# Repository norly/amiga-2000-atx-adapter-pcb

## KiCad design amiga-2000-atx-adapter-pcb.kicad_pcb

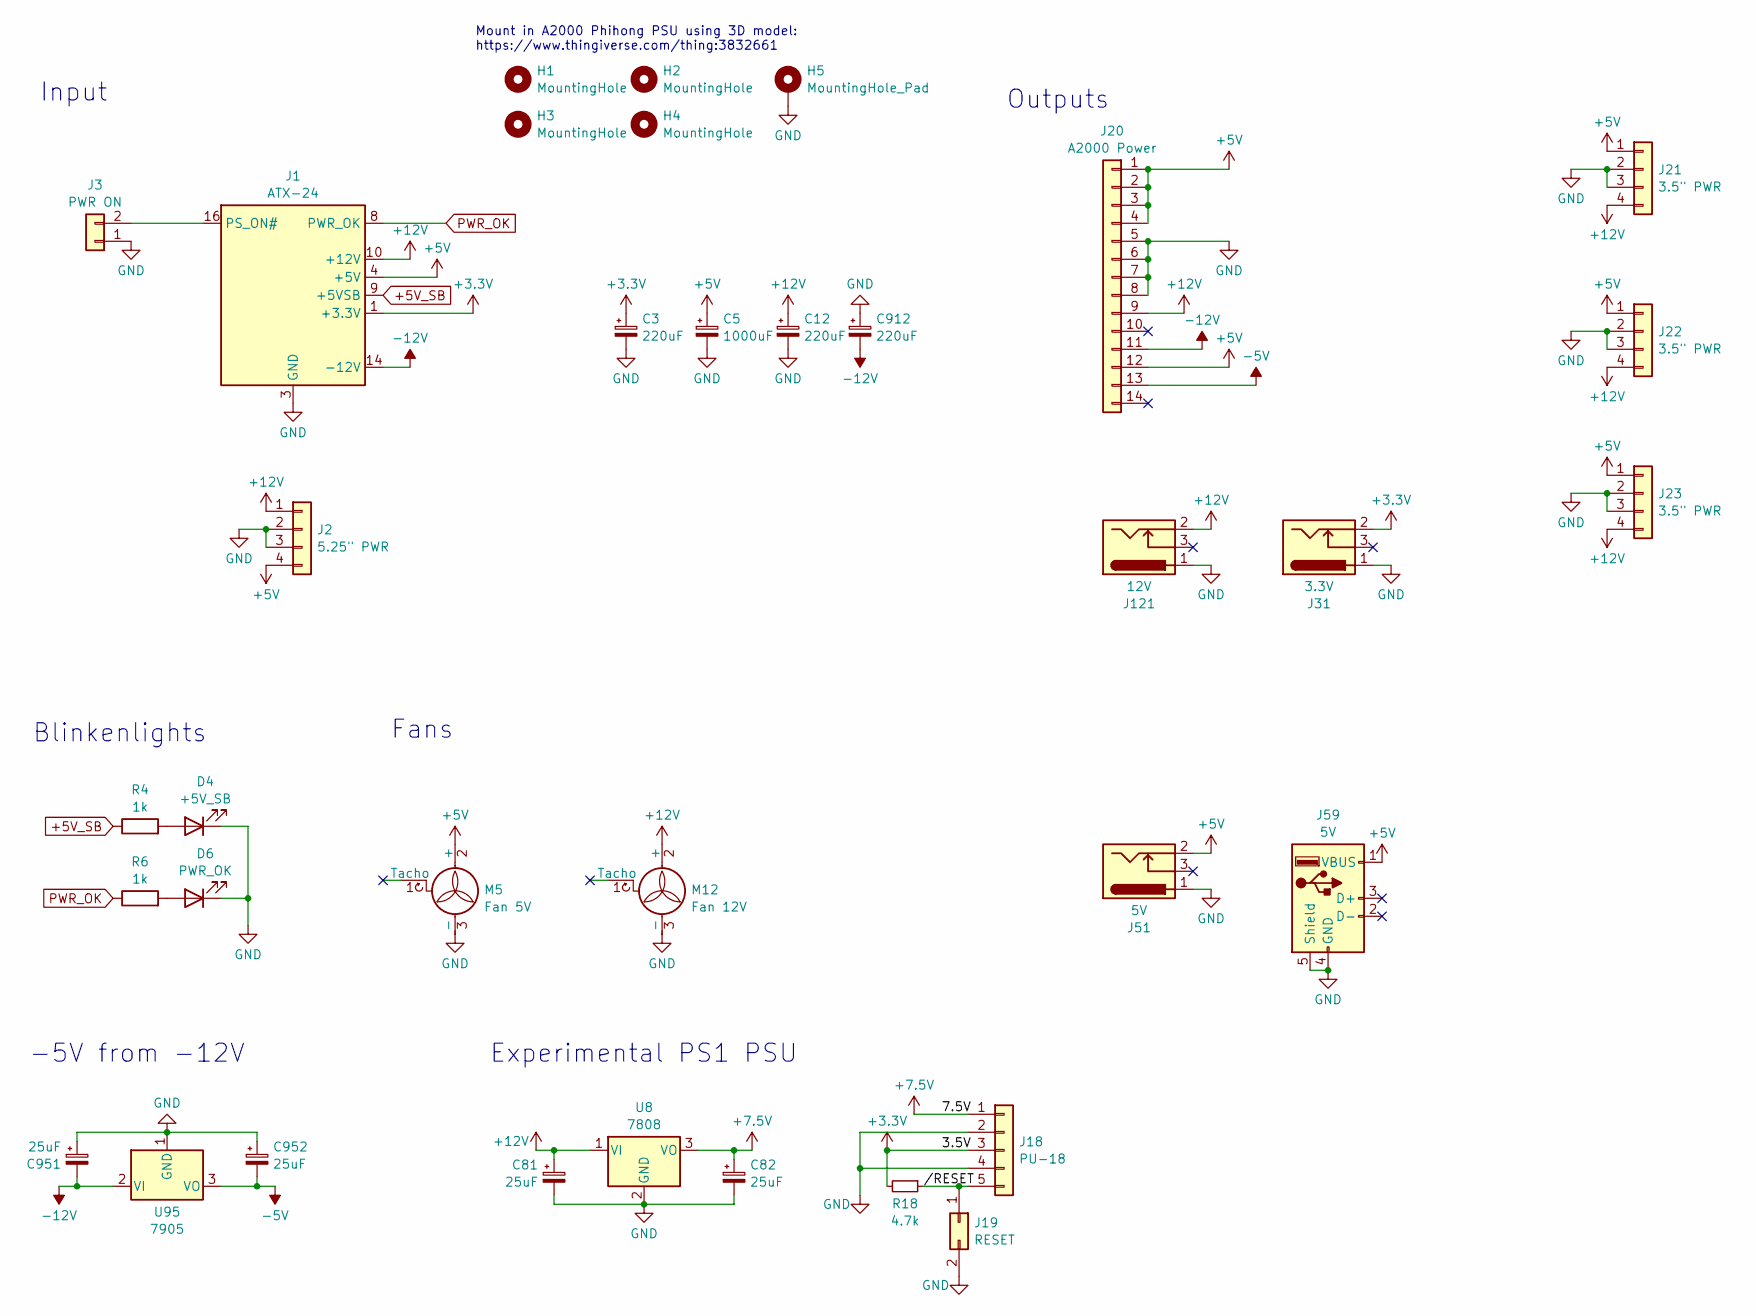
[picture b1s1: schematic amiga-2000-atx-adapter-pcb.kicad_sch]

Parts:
C3, C12, C912: 220uF; CP_Radial_D6.3mm_P2.50mm; LCSC C5438671
C5: 1000uF; CP_Radial_D10.0mm_P5.00mm; LCSC C5438717
C81, C82, C951, C952: 25uF; CP_Radial_D6.3mm_P2.50mm; LCSC C5438878
D4: +5V_SB; LED_D3.0mm; LCSC C6916234
D6: PWR_OK; LED_D3.0mm; LCSC C6916232
H1, H2, H3, H4: MountingHole; MountingHole_4mm
H5: MountingHole_Pad; MountingHole_3.2mm_M3_Pad
J1: ATX-24; Molex_Mini-Fit_Jr_5566-24A_2x12_P4.20mm_Vertical; LCSC C492537
J2: 5.25" PWR; TE_MATE-N-LOK_350211-1_1x04_P5.08mm_Vertical; LCSC C305826
J3: PWR ON; PinHeader_1x02_P2.54mm_Vertical; LCSC C358684
J18: PU-18; JST_EH_B5B-EH-A_1x05_P2.50mm_Vertical; LCSC C265084
J19: RESET; PinHeader_2x01_P2.54mm_Vertical
J20: A2000 Power; Molex_KK-396_A-41791-0014_1x14_P3.96mm_Vertical; LCSC C22394615
J21, J22, J23: 3.5" PWR; PinHeader_1x04_P2.54mm_Vertical; LCSC C210162
J31: 3.3V; BarrelJack_Horizontal; LCSC C22459640
J51: 5V; BarrelJack_Horizontal; LCSC C22459640
J59: 5V; USB_A_CONNFLY_DS1095-WNR0; LCSC C503996
J121: 12V; BarrelJack_Horizontal; LCSC C22459640
M5: Fan 5V; FanPinHeader_1x03_P2.54mm_Vertical; LCSC C843332
M12: Fan 12V; FanPinHeader_1x03_P2.54mm_Vertical; LCSC C843332
R4, R6: 1k; R_Axial_DIN0207_L6.3mm_D2.5mm_P7.62mm_Horizontal; LCSC C513706
R18: 4.7k; R_0603_1608Metric_Pad0.98x0.95mm_HandSolder
U8: 7808; TO-263-3_TabPin2; LCSC C7432228
U95: 7905; TO-263-3_TabPin2; LCSC C28684

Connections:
+3.3V: C3.1, J1.1 (+3.3V), J1.2 (+3.3V), J1.12 (+3.3V), J1.13 (+3.3V), J18.3, J31.2, R18.2
+5V: C5.1, J1.4 (+5V), J1.6 (+5V), J1.21 (+5V), J1.22 (+5V), J1.23 (+5V), J2.4, J20.1, J20.2, J20.3, J20.4, J20.12, J21.1, J22.1, J23.1, J51.2, J59.1 (VBUS), M5.2 (+)
+5V_SB: J1.9 (+5VSB), R4.1
+7.5V: C82.1, J18.1, U8.3 (VO)
+12V: C12.1, C81.1, J1.10 (+12V), J1.11 (+12V), J2.1, J20.9, J21.4, J22.4, J23.4, J121.2, M12.2 (+), U8.1 (VI)
-5V: C952.2, J20.13, U95.3 (VO)
-12V: C912.2, C951.2, J1.14 (-12V), J20.11, U95.2 (VI)
//RESET: J18.5, J19.1, R18.1
GND: C3.2, C5.2, C12.2, C81.2, C82.2, C912.1, C951.1, C952.1, D4.1 (K), D6.1 (K), H5.1, J1.3 (GND), J1.5 (GND), J1.7 (GND), J1.15 (GND), J1.17 (GND), J1.18 (GND), J1.19 (GND), J1.24 (GND), J2.2, J2.3, J3.1, J18.2, J18.4, J19.2, J20.5, J20.6, J20.7, J20.8, J21.2, J21.3, J22.2, J22.3, J23.2, J23.3, J31.1, J51.1, J59.4 (GND), J59.5 (Shield), J121.1, M5.3 (-), M12.3 (-), U8.2 (GND), U95.1 (GND)
unnamed: D4.2 (A), R4.2
unnamed: D6.2 (A), R6.2
unnamed: J1.16 (PS_ON#), J3.2
PWR_OK: J1.8 (PWR_OK), R6.1

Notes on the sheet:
Input
-5V from -12V
Fans
Mount in A2000 Phihong PSU using 3D model: https://www.thingiverse.com/thing:3832661
Experimental PS1 PSU
Blinkenlights
Outputs

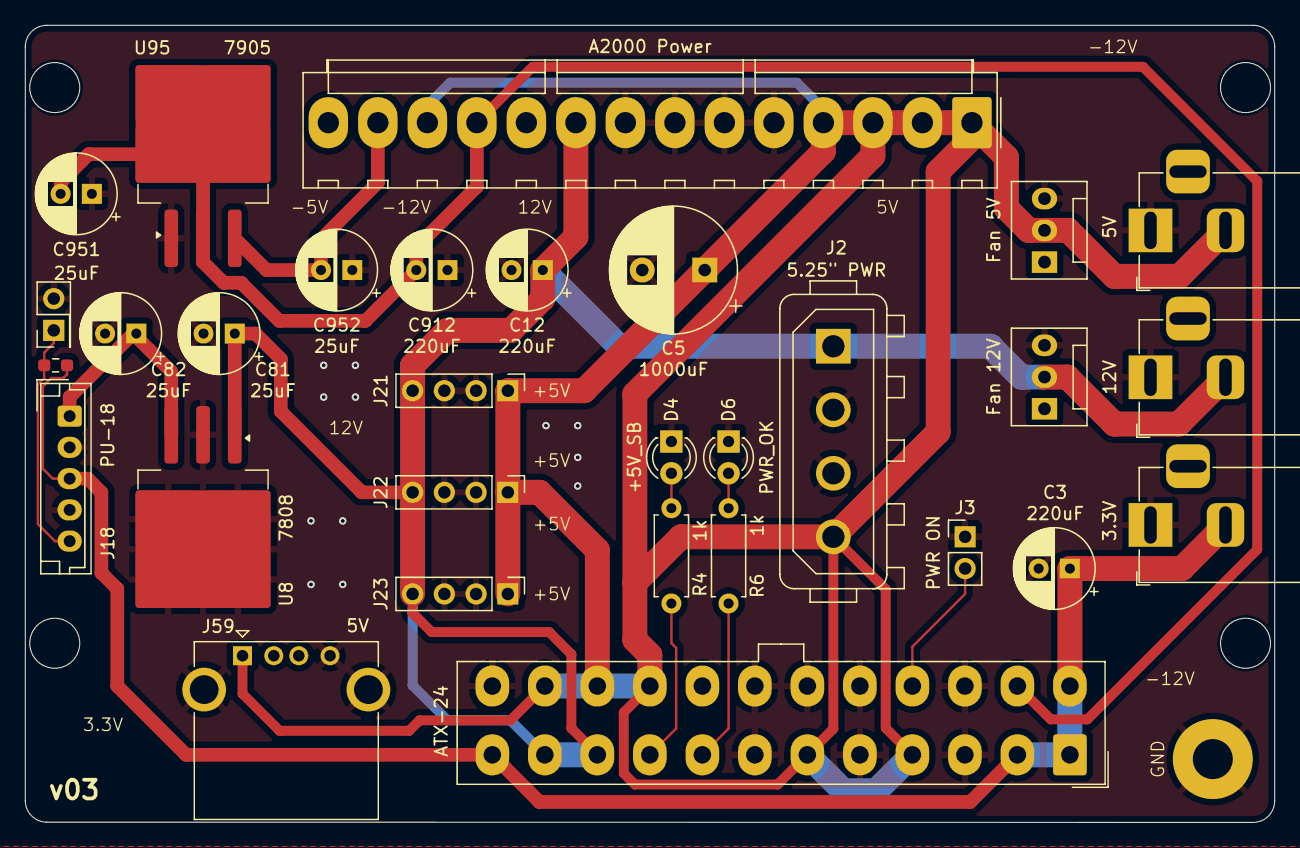
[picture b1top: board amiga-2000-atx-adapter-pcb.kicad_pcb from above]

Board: 2 copper layers, 99.9 x 63.8 mm, 35 parts (0 on the bottom side), 13 nets.

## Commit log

2024-09-30 Add .gitignore
2024-10-08 v02: Add ground pad
2024-10-28 v03: Add PS1 reset switch, remove one 3.5" connector
    The 3.5" power connectors were spaced too close together.
2024-11-02 LICENSE: CC0
